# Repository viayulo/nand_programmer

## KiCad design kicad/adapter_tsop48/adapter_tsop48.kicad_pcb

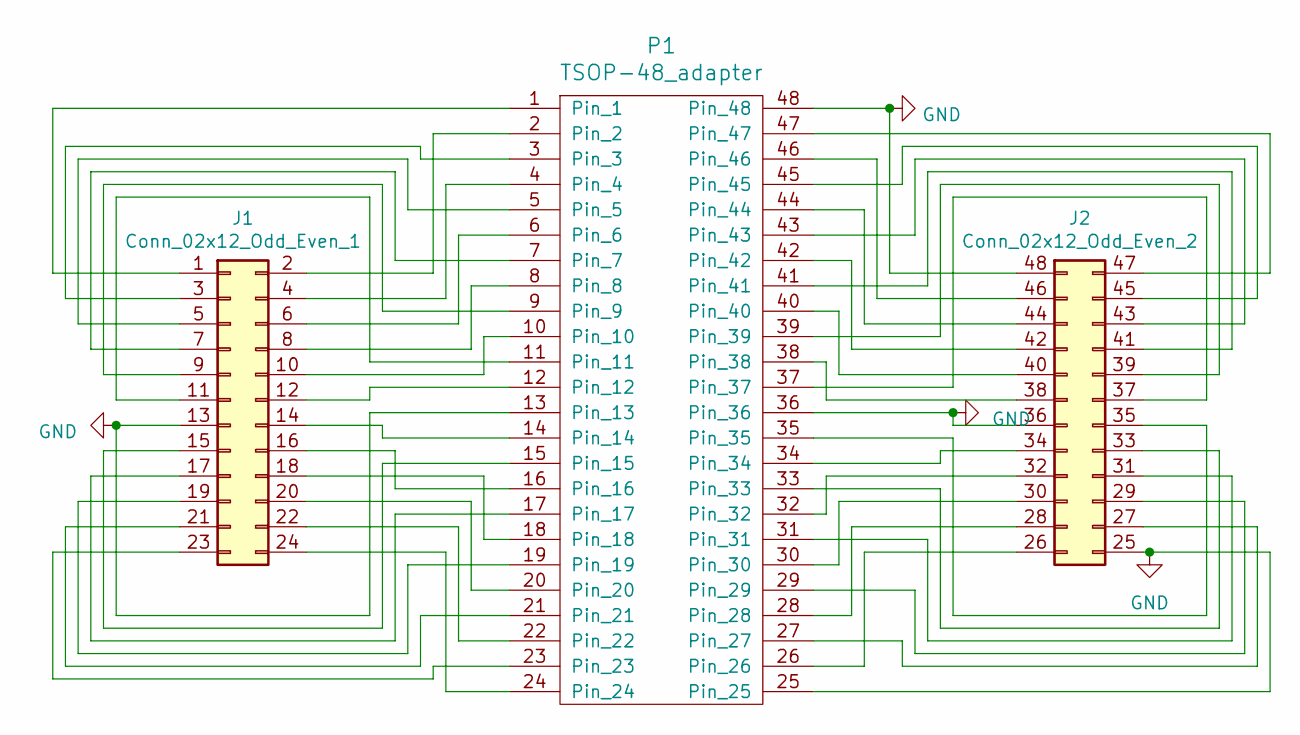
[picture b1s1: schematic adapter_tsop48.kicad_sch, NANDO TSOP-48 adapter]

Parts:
J1: Conn_02x12_Odd_Even_1; PinSocket_2x12_P2.54mm_Vertical
J2: Conn_02x12_Odd_Even_2; PinSocket_2x12_P2.54mm_Vertical_2
P1: TSOP-48_adapter; TSOP-48

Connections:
GND: J1.13, J2.25, J2.36, J2.48, P1.13, P1.25, P1.36, P1.48
unnamed: J1.1, P1.1
unnamed: J1.2, P1.2
unnamed: J1.3, P1.3
unnamed: J1.4, P1.4
unnamed: J1.5, P1.5
unnamed: J1.6, P1.6
unnamed: J1.7, P1.7
unnamed: J1.8, P1.8
unnamed: J1.9, P1.9
unnamed: J1.10, P1.10
unnamed: J1.11, P1.11
unnamed: J1.12, P1.12
unnamed: J1.14, P1.14
unnamed: J1.15, P1.15
unnamed: J1.16, P1.16
unnamed: J1.17, P1.17
unnamed: J1.18, P1.18
unnamed: J1.19, P1.19
unnamed: J1.20, P1.20
unnamed: J1.21, P1.21
unnamed: J1.22, P1.22
unnamed: J1.23, P1.23
unnamed: J1.24, P1.24
unnamed: J2.26, P1.26
unnamed: J2.27, P1.27
unnamed: J2.28, P1.28
unnamed: J2.29, P1.29
unnamed: J2.30, P1.30
unnamed: J2.31, P1.31
unnamed: J2.32, P1.32
unnamed: J2.33, P1.33
unnamed: J2.34, P1.34
unnamed: J2.35, P1.35
unnamed: J2.37, P1.37
unnamed: J2.38, P1.38
unnamed: J2.39, P1.39
unnamed: J2.40, P1.40
unnamed: J2.41, P1.41
unnamed: J2.42, P1.42
unnamed: J2.43, P1.43
unnamed: J2.44, P1.44
unnamed: J2.45, P1.45
unnamed: J2.46, P1.46
unnamed: J2.47, P1.47

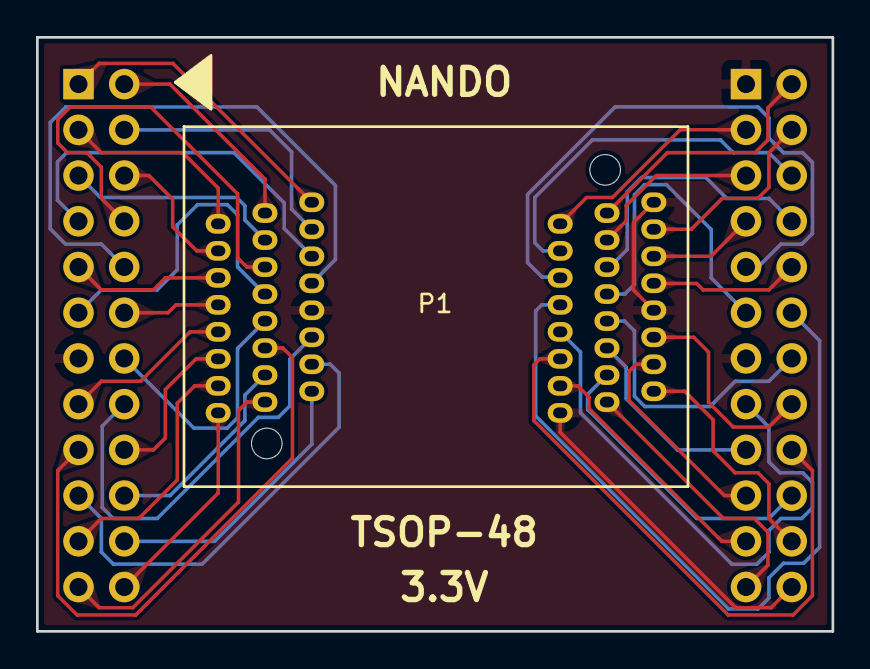
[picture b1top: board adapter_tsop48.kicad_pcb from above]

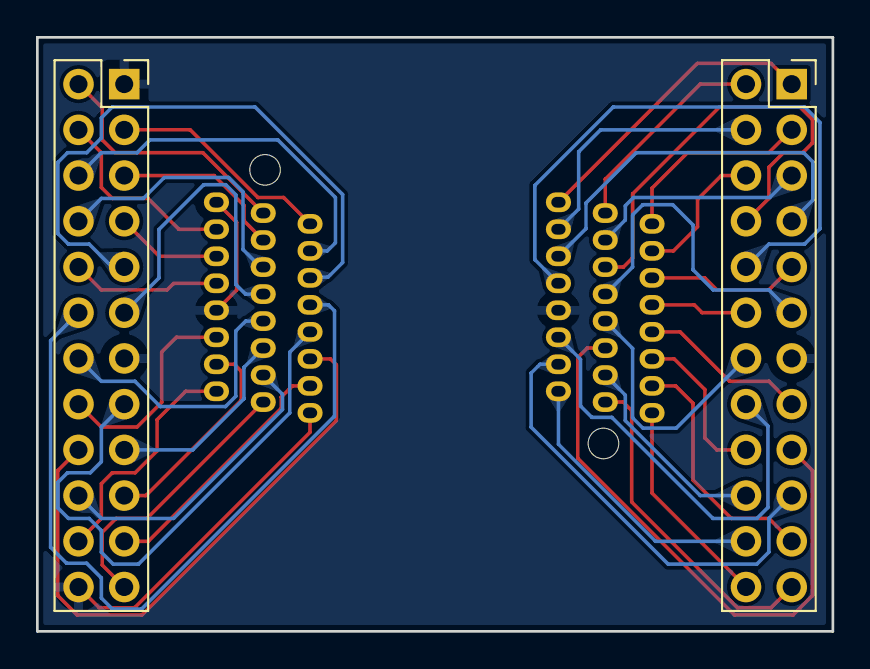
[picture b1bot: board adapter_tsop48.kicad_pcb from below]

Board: 2 copper layers, 44.2 x 33.0 mm, 3 parts (2 on the bottom side), 45 nets.

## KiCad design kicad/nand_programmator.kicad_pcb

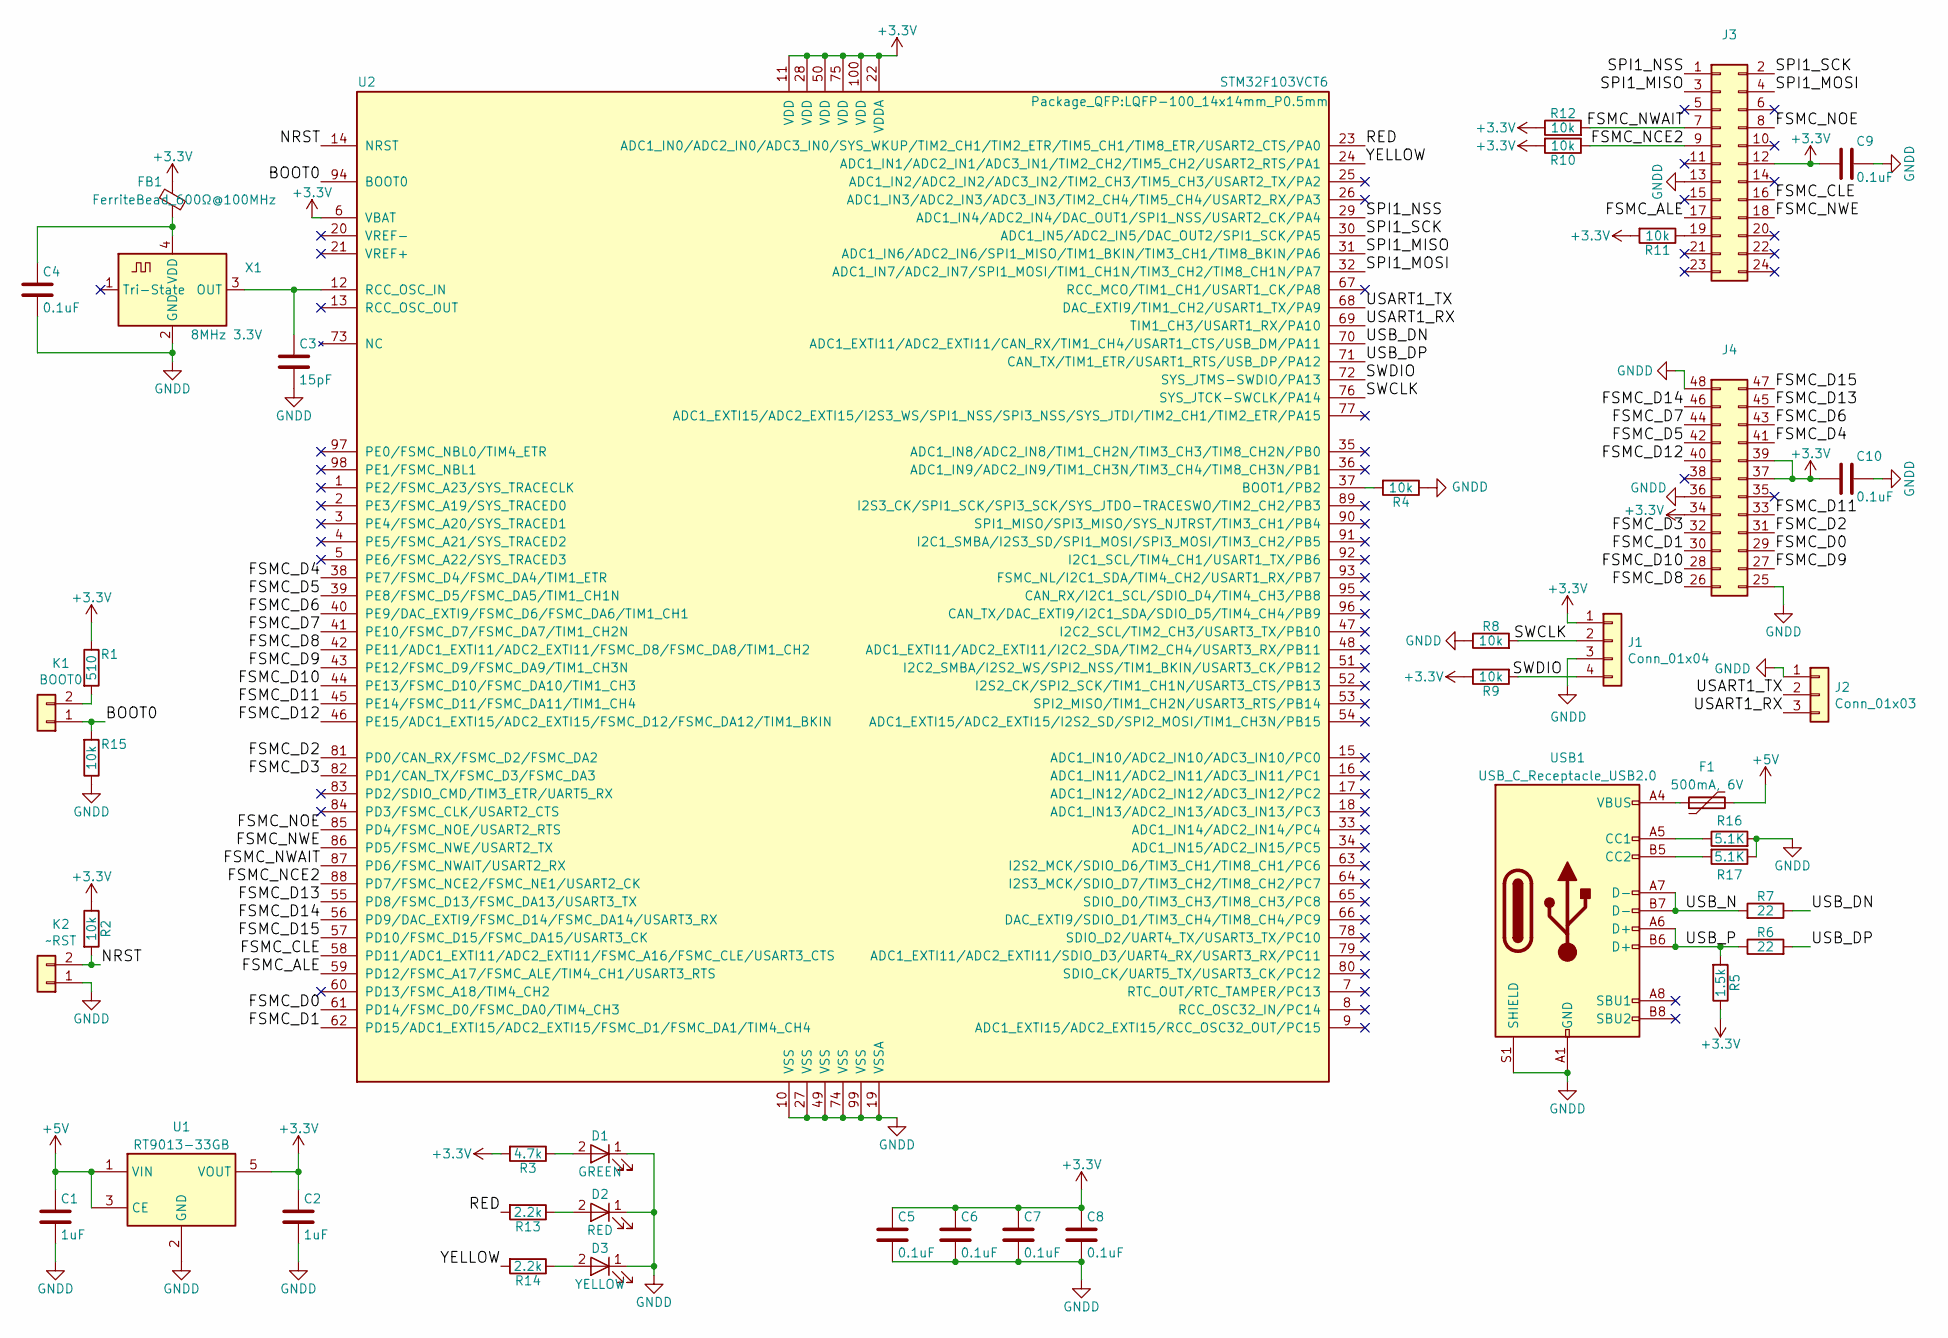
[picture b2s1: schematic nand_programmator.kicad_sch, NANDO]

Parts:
C1, C2: 1uF; C_0603_1608Metric_Pad1.08x0.95mm_HandSolder; Farnell Ref 2112850
C3: 15pF; C_0603_1608Metric_Pad1.08x0.95mm_HandSolder; Farnell Ref 2320839
C4, C5, C6, C7, C8, C9, C10: 0.1uF; C_0603_1608Metric_Pad1.08x0.95mm_HandSolder; Farnell Ref 2320839
D1: GREEN; LED_0603_1608Metric_Pad1.05x0.95mm_HandSolder; Farnell Ref 2099239
D2: RED; LED_0603_1608Metric_Pad1.05x0.95mm_HandSolder; Farnell Ref 2099236
D3: YELLOW; LED_0603_1608Metric_Pad1.05x0.95mm_HandSolder; Farnell Ref 2099243
F1: 500mA, 6V; Fuse_0603_1608Metric_Pad1.05x0.95mm_HandSolder
FB1: FerriteBead_600Ω@100MHz; R_0603_1608Metric_Pad0.98x0.95mm_HandSolder
J1: Conn_01x04; PinHeader_1x04_P2.54mm_Vertical; Farnell Ref 3049529
J2: Conn_01x03; PinHeader_1x03_P2.54mm_Vertical; Farnell Ref 3049527
J3: Conn_02x12_Odd_Even_Left; PinHeader_2x12_P2.54mm_Vertical; Farnell Ref 3049468
J4: Conn_02x12_Odd_Even_Right; PinHeader_2x12_P2.54mm_Vertical_2; Farnell Ref 3049468
K1: BOOT0; SW_Push_SPST_NO_Alps_SKRK
K2: ~RST; SW_Push_SPST_NO_Alps_SKRK
R1: 510; R_0603_1608Metric_Pad0.98x0.95mm_HandSolder; Farnell Ref 2447679
R2, R4, R8, R9, R10, R11, R12, R15: 10k; R_0603_1608Metric_Pad0.98x0.95mm_HandSolder; Farnell Ref 2447553
R3: 4.7k; R_0603_1608Metric_Pad0.98x0.95mm_HandSolder; Farnell Ref 2447587
R5: 1.5k; R_0603_1608Metric_Pad0.98x0.95mm_HandSolder; Farnell Ref 2447592
R6, R7: 22; R_0603_1608Metric_Pad0.98x0.95mm_HandSolder; Farnell Ref 2447609
R13, R14: 2.2k; R_0603_1608Metric_Pad0.98x0.95mm_HandSolder; Farnell Ref 2447587
R16, R17: 5.1K; R_0603_1608Metric_Pad0.98x0.95mm_HandSolder
U1: RT9013-33GB; SOT-23-5
U2: STM32F103VCT6; LQFP-100_14x14mm_P0.5mm; Farnell Ref 1624139
USB1: USB_C_Receptacle_USB2.0; USB_C_Receptacle_GCT_USB4105-xx-A_16P_TopMnt_Horizontal
X1: 8MHz 3.3V; Oscillator_SMD_Abracon_ASE-4Pin_3.2x2.5mm_HandSoldering

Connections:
+3V3: C2.1, C5.1, C6.1, C7.1, C8.1, C9.2, C10.2, FB1.1, J1.1, J3.12, J4.34, J4.37, J4.39, R1.1, R2.1, R3.2, R5.1, R9.1, R10.2, R11.2, R12.1, U1.5 (VOUT), U2.6 (VBAT), U2.11 (VDD), U2.22 (VDDA), U2.28 (VDD), U2.50 (VDD), U2.75 (VDD), U2.100 (VDD)
+5V: C1.1, F1.2, U1.1 (VIN), U1.3 (CE)
/BOOT0: K1.1, R15.2, U2.94 (BOOT0)
/FSMC_ALE: J3.17, U2.59 (PD12/FSMC_A17/FSMC_ALE/TIM4_CH1/USART3_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)
/FSMC_CLE: J3.16, U2.58 (PD11/ADC1_EXTI11/ADC2_EXTI11/FSMC_A16/F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)
/FSMC_D0: J4.29, U2.61 (PD14/FSMC_D0/FSMC_DA0/TIM4_CH3)
/FSMC_D1: J4.30, U2.62 (PD15/ADC1_EXTI15/ADC2_EXTI15/FSMC_D1/FS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)
/FSMC_D2: J4.31, U2.81 (PD0/CAN_RX/FSMC_D2/FSMC_DA2)
/FSMC_D3: J4.32, U2.82 (PD1/CAN_TX/FSMC_D3/FSMC_DA3)
/FSMC_D4: J4.41, U2.38 (PE7/FSMC_D4/FSMC_DA4/TIM1_ETR)
/FSMC_D5: J4.42, U2.39 (PE8/FSMC_D5/FSMC_DA5/TIM1_CH1N)
/FSMC_D6: J4.43, U2.40 (PE9/DAC_EXTI9/FSMC_D6/FSMC_DA6/TIM1_CH1)
/FSMC_D7: J4.44, U2.41 (PE10/FSMC_D7/FSMC_DA7/TIM1_CH2N)
/FSMC_D8: J4.26, U2.42 (PE11/ADC1_EXTI11/ADC2_EXTI11/FSMC_D8/FS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)
/FSMC_D9: J4.27, U2.43 (PE12/FSMC_D9/FSMC_DA9/TIM1_CH3N)
/FSMC_D10: J4.28, U2.44 (PE13/FSMC_D10/FSMC_DA10/TIM1_CH3)
/FSMC_D11: J4.33, U2.45 (PE14/FSMC_D11/FSMC_DA11/TIM1_CH4)
/FSMC_D12: J4.40, U2.46 (PE15/ADC1_EXTI15/ADC2_EXTI15/FSMC_D12/F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)
/FSMC_D13: J4.45, U2.55 (PD8/FSMC_D13/FSMC_DA13/USART3_TX)
/FSMC_D14: J4.46, U2.56 (PD9/DAC_EXTI9/FSMC_D14/FSMC_DA14/USART3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)
/FSMC_D15: J4.47, U2.57 (PD10/FSMC_D15/FSMC_DA15/USART3_CK)
/FSMC_NCE2: J3.9, R10.1, U2.88 (PD7/FSMC_NCE2/FSMC_NE1/USART2_CK)
/FSMC_NOE: J3.8, U2.85 (PD4/FSMC_NOE/USART2_RTS)
/FSMC_NWAIT: J3.7, R12.2, U2.87 (PD6/FSMC_NWAIT/USART2_RX)
/FSMC_NWE: J3.18, U2.86 (PD5/FSMC_NWE/USART2_TX)
/NRST: K2.2, R2.2, U2.14 (NRST)
/RED: R13.2, U2.23 (ADC1_IN0/ADC2_IN0/ADC3_IN0/SYS_WKUP/TIM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)
/SPI1_MISO: J3.3, U2.31 (ADC1_IN6/ADC2_IN6/SPI1_MISO/TIM1_BKIN/T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)
/SPI1_MOSI: J3.4, U2.32 (ADC1_IN7/ADC2_IN7/SPI1_MOSI/TIM1_CH1N/T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)
/SPI1_NSS: J3.1, U2.29 (ADC1_IN4/ADC2_IN4/DAC_OUT1/SPI1_NSS/USA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)
/SPI1_SCK: J3.2, U2.30 (ADC1_IN5/ADC2_IN5/DAC_OUT2/SPI1_SCK/PA5)
/SWCLK: J1.2, R8.2, U2.76 (SYS_JTCK-SWCLK/PA14)
/SWDIO: J1.4, R9.2, U2.72 (SYS_JTMS-SWDIO/PA13)
/USART1_RX: J2.3, U2.69 (TIM1_CH3/USART1_RX/PA10)
/USART1_TX: J2.2, U2.68 (DAC_EXTI9/TIM1_CH2/USART1_TX/PA9)
/USB_DN: R7.1, U2.70 (ADC1_EXTI11/ADC2_EXTI11/CAN_RX/TIM1_CH4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)
/USB_DP: R6.2, U2.71 (CAN_TX/TIM1_ETR/USART1_RTS/USB_DP/PA12)
/USB_N: R7.2, USB1.A7 (D-), USB1.B7 (D-)
/USB_P: R5.2, R6.1, USB1.A6 (D+), USB1.B6 (D+)
/YELLOW: R14.2, U2.24 (ADC1_IN1/ADC2_IN1/ADC3_IN1/TIM2_CH2/TIM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)
GNDD: C1.2, C2.2, C3.2, C4.2, C5.2, C6.2, C7.2, C8.2, C9.1, C10.1, D1.1 (K), D2.1 (K), D3.1 (K), J1.3, J2.1, J3.13, J4.25, J4.36, J4.48, K2.1, R4.1, R8.1, R15.1, R16.2, R17.1, U1.2 (GND), U2.10 (VSS), U2.19 (VSSA), U2.27 (VSS), U2.49 (VSS), U2.74 (VSS), U2.99 (VSS), USB1.A1 (GND), USB1.A12 (GND), USB1.B1 (GND), USB1.B12 (GND), USB1.S1 (SHIELD), X1.2 (GND)
unnamed: D1.2 (A), R3.1
unnamed: D2.2 (A), R13.1
unnamed: D3.2 (A), R14.1
unnamed: F1.1, USB1.A4 (VBUS), USB1.A9 (VBUS), USB1.B4 (VBUS), USB1.B9 (VBUS)
unnamed: J3.19, R11.1
unnamed: K1.2, R1.2
unnamed: R4.2, U2.37 (BOOT1/PB2)
unnamed: C3.1, U2.12 (RCC_OSC_IN), X1.3 (OUT)
unnamed: R16.1, USB1.A5 (CC1)
unnamed: R17.2, USB1.B5 (CC2)
unnamed: C4.1, FB1.2, X1.4 (VDD)

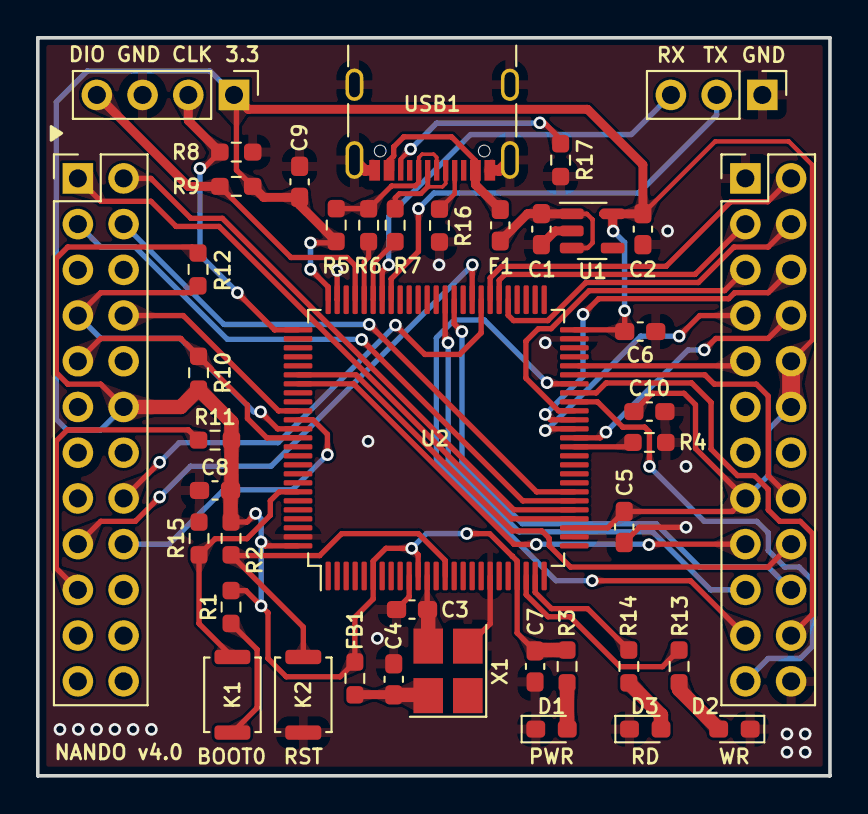
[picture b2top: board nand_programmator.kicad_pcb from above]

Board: 2 copper layers, 44.0 x 41.0 mm, 42 parts (0 on the bottom side), 52 nets.

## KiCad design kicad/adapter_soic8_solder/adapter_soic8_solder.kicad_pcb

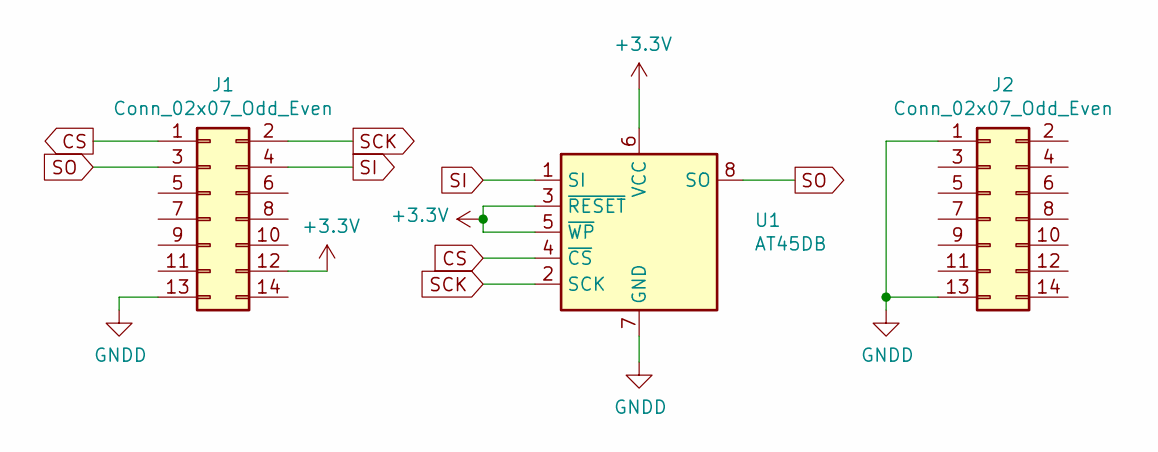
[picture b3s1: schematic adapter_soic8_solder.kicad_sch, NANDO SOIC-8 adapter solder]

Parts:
J1, J2: Conn_02x07_Odd_Even; PinSocket_2x07_P2.54mm_Vertical; Farnell Ref 1392520
U1: AT45DB; SOIC-8_3.9x4.9mm_P1.27mm

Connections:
+3V3: J1.12, U1.3 (~RESET), U1.5 (~WP), U1.6 (VCC)
CS: J1.1, U1.4 (~CS)
GNDD: J1.13, J2.1, J2.13, U1.7 (GND)
SCK: J1.2, U1.2 (SCK)
SI: J1.4, U1.1 (SI)
SO: J1.3, U1.8 (SO)

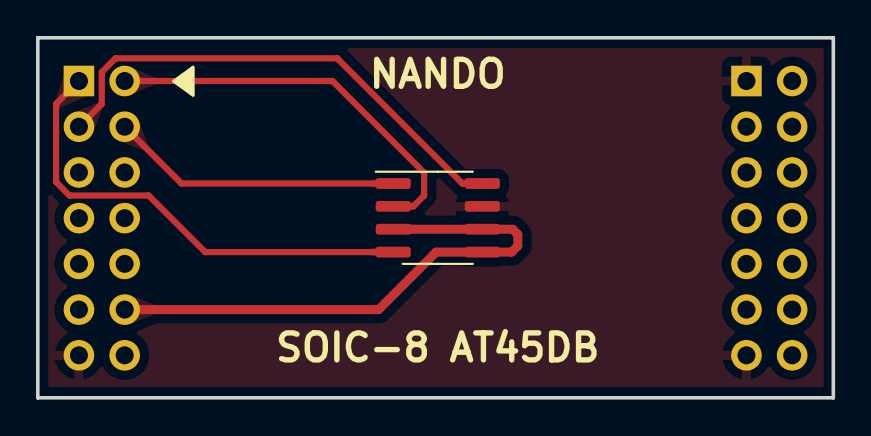
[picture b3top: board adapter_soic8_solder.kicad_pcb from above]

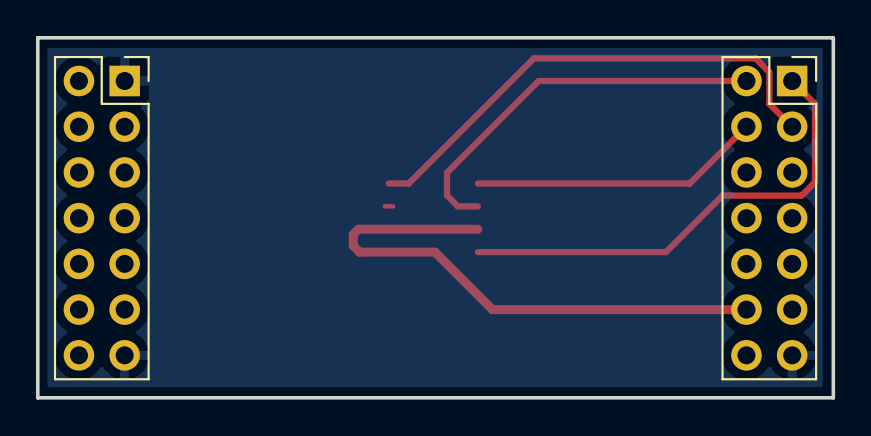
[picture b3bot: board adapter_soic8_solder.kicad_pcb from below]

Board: 2 copper layers, 44.2 x 20.0 mm, 3 parts (2 on the bottom side), 6 nets.

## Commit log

2023-10-20 update PCB design and cleanup KiCad files
